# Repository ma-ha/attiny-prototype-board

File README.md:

# ATtiny Prototype Board v2

Simplifies circuit prototypying with the ATtiny xx14.

Features:
- Beadboard (400 pins)
- I/O
  - 4x LED
  - 3x Potentiometer
  - 2x momentary push button
  - 4x Switch
  - 2x 3.5 mm TRS socket
  - 4x banana socket
  - 2/3x I2C
  - 2x Serial
- ATtiny XX14
- FTDI adapter (CH340E Micro USB Serial adapter)
  - UPDI programming
  - USB power
  - Serial debugging

Videos:
- Build: https://youtu.be/CmCrIgkOkTU (no talking)
- Description https://youtu.be/84AR5vEIgwg (German)

# Links

- megaTinyCore Core: https://github.com/SpenceKonde/megaTinyCore
- ATtiny xx14 Pinout https://github.com/SpenceKonde/megaTinyCore/blob/master/megaavr/extras/ATtiny_x14.md
- Installation in Arduino IDE: https://github.com/SpenceKonde/megaTinyCore/blob/master/Installation.md

# Release Notes

## v2.1 changes

Improvements:
- Switch (optional) for I2C
- I2C labels and lines
- Push buttons with opener and closer funtionality
- Moved USART 

Fixes: 
- banana sockets were too close to border
- more space between switches and TRS

## v2.0 changes

- use THT LEDs, resistors, diode
- use slide switch: more reliable and visible
- use only socket header

# Blink All

Use this "blink" code to check proper soldering for all ATtiny pins:

    // BLINK ALL ATtiny xx14

    void setup() {
      pinMode( PIN_PA4, OUTPUT );
      pinMode( PIN_PA5, OUTPUT );
      pinMode( PIN_PA6, OUTPUT );
      pinMode( PIN_PA7, OUTPUT );
      pinMode( PIN_PB3, OUTPUT );
      pinMode( PIN_PB2, OUTPUT );
      
      pinMode( PIN_PB1, OUTPUT );
      pinMode( PIN_PB0, OUTPUT );
      pinMode( PIN_PA0, OUTPUT );
      pinMode( PIN_PA1, OUTPUT );
      pinMode( PIN_PA2, OUTPUT );
      pinMode( PIN_PA3, OUTPUT );
      Serial.begin( 9600 );
    }

    void loop() {
      digitalWrite( PIN_PA4, HIGH );   
      digitalWrite( PIN_PA5, HIGH );   
      digitalWrite( PIN_PA6, HIGH );   
      digitalWrite( PIN_PA7, HIGH );   
      digitalWrite( PIN_PB3, HIGH );   
      digitalWrite( PIN_PB2, HIGH );
        
      digitalWrite( PIN_PB1, HIGH );   
      digitalWrite( PIN_PB0, HIGH );   
      digitalWrite( PIN_PA0, HIGH );   
      digitalWrite( PIN_PA1, HIGH );   
      digitalWrite( PIN_PA2, HIGH );   
      digitalWrite( PIN_PA3, HIGH );   
      Serial.println( "on" );
      delay( 500 );                       
      
      digitalWrite( PIN_PA4, LOW );   
      digitalWrite( PIN_PA5, LOW );   
      digitalWrite( PIN_PA6, LOW );   
      digitalWrite( PIN_PA7, LOW );   
      digitalWrite( PIN_PB3, LOW );   
      digitalWrite( PIN_PB2, LOW );
        
      digitalWrite( PIN_PB1, LOW );   
      digitalWrite( PIN_PB0, LOW );   
      digitalWrite( PIN_PA0, LOW );   
      digitalWrite( PIN_PA1, LOW );   
      digitalWrite( PIN_PA2, LOW );   
      digitalWrite( PIN_PA3, LOW );   
      Serial.println( "off" );
      delay( 500 );                     
    }

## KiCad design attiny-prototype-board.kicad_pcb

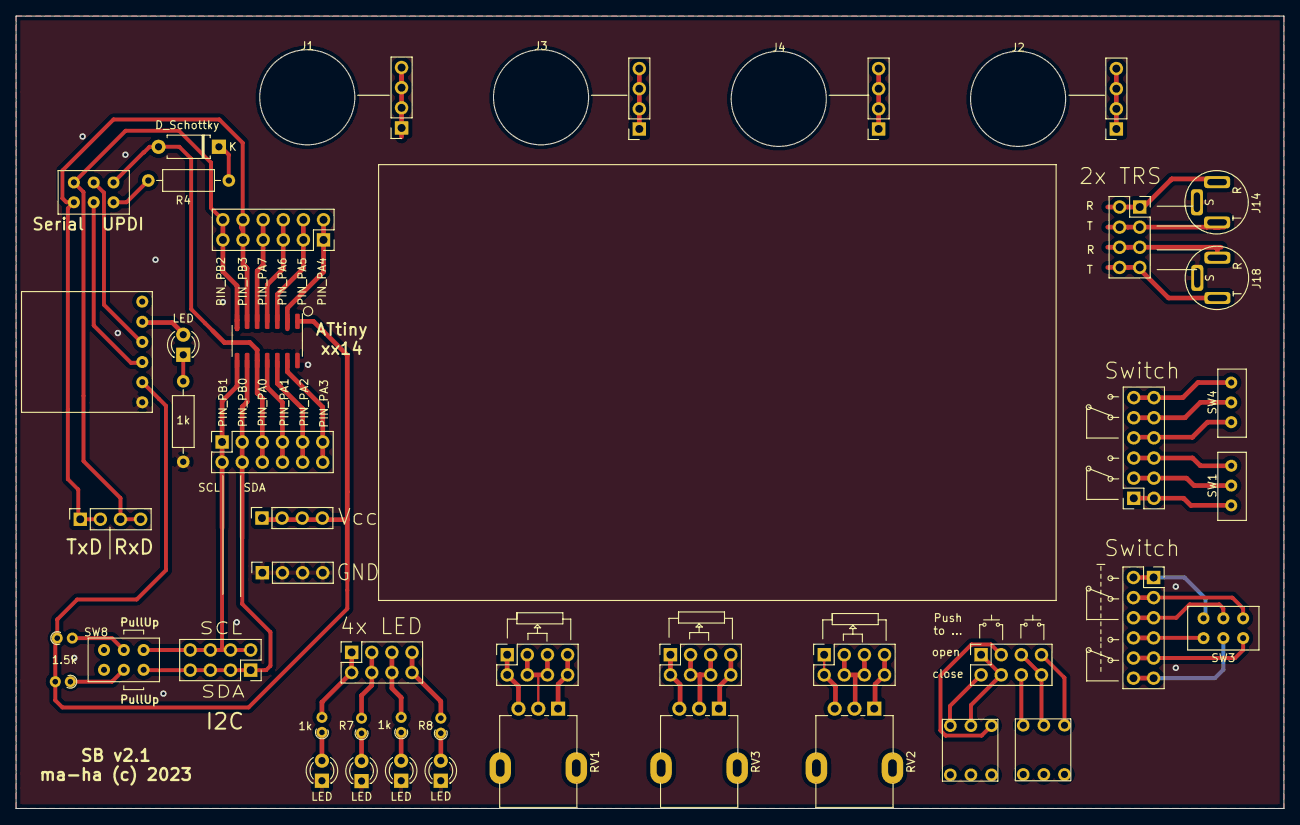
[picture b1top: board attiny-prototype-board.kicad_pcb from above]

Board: 2 copper layers, 160.0 x 100.0 mm, 50 parts (0 on the bottom side), 65 nets.

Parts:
1k: 1k; R_Axial_DIN0207_L6.3mm_D2.5mm_P10.16mm_Horizontal
D1, D2, D3, D5, D6: LED; LED_D3.0mm
D4: D_Schottky; D_A-405_P7.62mm_Horizontal
J1, J2, J3, J4: Banana
J5, J7, J8: tinyRight; PinSocket_2x06_P2.54mm_Vertical
J6, J15, J19, J22: toPoti; PinSocket_2x04_P2.54mm_Vertical
J9, J10, J11, J12: banana; PinSocket_1x04_P2.54mm_Vertical
J13: tinyLeft; PinSocket_2x06_P2.54mm_Vertical
J14, J18: TRS35; Stereo3.5
J16: toAudio; PinSocket_2x04_P2.54mm_Vertical
J17: USART; PinSocket_1x04_P2.54mm_Vertical
J20: GND; PinSocket_1x04_P2.54mm_Vertical
J21: toBtn; PinSocket_2x04_P2.54mm_Vertical
J23: VCC; PinSocket_1x04_P2.54mm_Vertical
J25: I2C; PinSocket_2x04_P2.54mm_Vertical
R1, R2, R7, R8: 1k; R_Axial_DIN0204_L3.6mm_D1.6mm_P1.90mm_Vertical
R4: 1k; R_Axial_DIN0207_L6.3mm_D2.5mm_P10.16mm_Horizontal
R5, R6: 1.5k; R_Axial_DIN0204_L3.6mm_D1.6mm_P1.90mm_Vertical
RV1, RV2, RV3: R_POT; Potentiometer_Single_Vertical
SW1, SW4: SW_SPDT; Switch_SPDT_1P2T
SW2: Switch UPDI; Switch_SPDT_2P2T
SW3, SW8: 2x Switch; Switch_SPDT_2P2T
SW9, SW10: SW_Push_DPDT; PushBtn6x6
U1: FTDI-Adapter; FTDI
U2: ATtinyXX14-SS; SOIC-14_3.9x8.7mm_P1.27mm

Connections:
FTDI-RXD: SW2.2, U1.3
FTDI-TXD: SW2.5, U1.4
GND: 1k.1, D1.1, D2.1, D5.1, D6.1, J14.2, J18.2, J20.1, J20.2, J20.3, J20.4, U1.6, U2.14
unnamed: D1.2, R1.1
unnamed: D2.2, R7.1
unnamed: 1k.2, D3.1
unnamed: D3.2, U1.2
unnamed: D4.1, R4.1
unnamed: D5.2, R2.1
unnamed: D6.2, R8.1
unnamed: J9.1, J9.2, J9.3, J9.4
unnamed: J5.1, J5.2, SW1.1
unnamed: J5.3, J5.4, SW1.2
unnamed: J5.5, J5.6, SW1.3
unnamed: J5.7, J5.8, SW4.1
unnamed: J5.9, J5.10, SW4.2
unnamed: J5.11, J5.12, SW4.3
unnamed: J6.1, J6.2, R1.2
unnamed: J6.3, J6.4, R7.2
unnamed: J6.5, J6.6, R2.2
unnamed: J6.7, J6.8, R8.2
unnamed: J8.1, J8.2, SW3.6
unnamed: J8.3, J8.4, SW3.4
unnamed: J8.5, J8.6, SW3.5
unnamed: J8.7, J8.8, SW3.3
unnamed: J8.9, J8.10, SW3.1
unnamed: J8.11, J8.12, SW3.2
unnamed: J10.1, J10.2, J10.3, J10.4
unnamed: J11.1, J11.2, J11.3, J11.4
unnamed: J12.1, J12.2, J12.3, J12.4
unnamed: J14.1, J16.3, J16.4
unnamed: J14.3, J16.1, J16.2
unnamed: J15.1, J15.2, RV1.3
unnamed: J15.3, J15.4, J15.5, J15.6, RV1.2
unnamed: J15.7, J15.8, RV1.1
unnamed: J16.5, J16.6, J18.3
unnamed: J16.7, J16.8, J18.1
unnamed: J19.1, J19.2, RV2.3
unnamed: J19.3, J19.4, J19.5, J19.6, RV2.2
unnamed: J19.7, J19.8, RV2.1
unnamed: J21.1, J21.4, SW10.2
unnamed: J21.2, SW10.1
unnamed: J21.3, SW10.3
unnamed: J21.5, J21.8, SW9.2
unnamed: J21.6, SW9.1
unnamed: J21.7, SW9.3
unnamed: J22.1, J22.2, RV3.3
unnamed: J22.3, J22.4, J22.5, J22.6, RV3.2
unnamed: J22.7, J22.8, RV3.1
unnamed: R4.2, SW2.6
unnamed: R5.1, SW8.5
unnamed: R6.2, SW8.2
RXD: J13.11, J13.12, J17.3, J17.4, SW2.1, U2.7
SCL: J7.1, J7.2, J25.2, J25.4, J25.6, J25.8, SW8.3, U2.8
SDA: J7.3, J7.4, J25.1, J25.3, J25.5, J25.7, SW8.6, U2.9
TXD: J13.9, J13.10, J17.1, J17.2, SW2.4, U2.6
TinyP1: J13.1, J13.2, U2.2
TinyP2: J13.3, J13.4, U2.3
TinyP3: J13.5, J13.6, U2.4
TinyP4: J13.7, J13.8, U2.5
TinyP9: D4.2, J7.5, J7.6, SW2.3, U2.10
TinyP10: J7.7, J7.8, U2.11
TinyP11: J7.9, J7.10, U2.12
TinyP12: J7.11, J7.12, U2.13
VCC: J23.1, J23.2, J23.3, J23.4, R5.2, R6.1, U1.5, U2.1

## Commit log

2023-12-16 v2 publish
2023-12-16 fix lib path
2023-12-16 improve docu
2023-12-16 spec for adapter
2023-12-23 v2.1 some improvements
2023-12-23 v2.1 move USART
2023-12-23 v2.0 photo
2023-12-24 "blink" test code

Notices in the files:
attiny-prototype-board.kicad_pcb:
ma-ha (c) 2023
